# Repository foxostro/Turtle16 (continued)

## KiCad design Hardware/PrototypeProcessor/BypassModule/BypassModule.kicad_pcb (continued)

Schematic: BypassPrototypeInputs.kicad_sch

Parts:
J1: Control Signals; PinHeader_1x10_P2.54mm_Vertical
J2: Y_EX; PinHeader_1x16_P2.54mm_Vertical
J3: Y_MEM; PinHeader_1x16_P2.54mm_Vertical
J4: RegisterA; PinHeader_1x16_P2.54mm_Vertical
J5: RegisterB; PinHeader_1x16_P2.54mm_Vertical

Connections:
/Bypass Prototype Inputs/FWD_A: J1.3; also elsewhere on the board
/Bypass Prototype Inputs/FWD_B: J1.6; also elsewhere on the board
/Bypass Prototype Inputs/FWD_EX_TO_A: J1.4; also elsewhere on the board
/Bypass Prototype Inputs/FWD_EX_TO_B: J1.7; also elsewhere on the board
/Bypass Prototype Inputs/FWD_MEM_TO_A: J1.5; also elsewhere on the board
/Bypass Prototype Inputs/FWD_MEM_TO_B: J1.8; also elsewhere on the board
/Bypass Prototype Inputs/Phi1d: J1.1; also elsewhere on the board
/Bypass Prototype Inputs/RegisterA0: J4.1; also elsewhere on the board
/Bypass Prototype Inputs/RegisterA1: J4.2; also elsewhere on the board
/Bypass Prototype Inputs/RegisterA2: J4.3; also elsewhere on the board
/Bypass Prototype Inputs/RegisterA3: J4.4; also elsewhere on the board
/Bypass Prototype Inputs/RegisterA4: J4.5; also elsewhere on the board
/Bypass Prototype Inputs/RegisterA5: J4.6; also elsewhere on the board
/Bypass Prototype Inputs/RegisterA6: J4.7; also elsewhere on the board
/Bypass Prototype Inputs/RegisterA7: J4.8; also elsewhere on the board
/Bypass Prototype Inputs/RegisterA8: J4.9; also elsewhere on the board
/Bypass Prototype Inputs/RegisterA9: J4.10; also elsewhere on the board
/Bypass Prototype Inputs/RegisterA10: J4.11; also elsewhere on the board
/Bypass Prototype Inputs/RegisterA11: J4.12; also elsewhere on the board
/Bypass Prototype Inputs/RegisterA12: J4.13; also elsewhere on the board
/Bypass Prototype Inputs/RegisterA13: J4.14; also elsewhere on the board
/Bypass Prototype Inputs/RegisterA14: J4.15; also elsewhere on the board
/Bypass Prototype Inputs/RegisterA15: J4.16; also elsewhere on the board
/Bypass Prototype Inputs/RegisterB0: J5.1; also elsewhere on the board
/Bypass Prototype Inputs/RegisterB1: J5.2; also elsewhere on the board
/Bypass Prototype Inputs/RegisterB2: J5.3; also elsewhere on the board
/Bypass Prototype Inputs/RegisterB3: J5.4; also elsewhere on the board
/Bypass Prototype Inputs/RegisterB4: J5.5; also elsewhere on the board
/Bypass Prototype Inputs/RegisterB5: J5.6; also elsewhere on the board
/Bypass Prototype Inputs/RegisterB6: J5.7; also elsewhere on the board
/Bypass Prototype Inputs/RegisterB7: J5.8; also elsewhere on the board
/Bypass Prototype Inputs/RegisterB8: J5.9; also elsewhere on the board
/Bypass Prototype Inputs/RegisterB9: J5.10; also elsewhere on the board
/Bypass Prototype Inputs/RegisterB10: J5.11; also elsewhere on the board
/Bypass Prototype Inputs/RegisterB11: J5.12; also elsewhere on the board
/Bypass Prototype Inputs/RegisterB12: J5.13; also elsewhere on the board
/Bypass Prototype Inputs/RegisterB13: J5.14; also elsewhere on the board
/Bypass Prototype Inputs/RegisterB14: J5.15; also elsewhere on the board
/Bypass Prototype Inputs/RegisterB15: J5.16; also elsewhere on the board
/Bypass Prototype Inputs/Y_EX0: J2.1; also elsewhere on the board
/Bypass Prototype Inputs/Y_EX1: J2.2; also elsewhere on the board
/Bypass Prototype Inputs/Y_EX2: J2.3; also elsewhere on the board
/Bypass Prototype Inputs/Y_EX3: J2.4; also elsewhere on the board
/Bypass Prototype Inputs/Y_EX4: J2.5; also elsewhere on the board
/Bypass Prototype Inputs/Y_EX5: J2.6; also elsewhere on the board
/Bypass Prototype Inputs/Y_EX6: J2.7; also elsewhere on the board
/Bypass Prototype Inputs/Y_EX7: J2.8; also elsewhere on the board
/Bypass Prototype Inputs/Y_EX8: J2.9; also elsewhere on the board
/Bypass Prototype Inputs/Y_EX9: J2.10; also elsewhere on the board
/Bypass Prototype Inputs/Y_EX10: J2.11; also elsewhere on the board
/Bypass Prototype Inputs/Y_EX11: J2.12; also elsewhere on the board
/Bypass Prototype Inputs/Y_EX12: J2.13; also elsewhere on the board
/Bypass Prototype Inputs/Y_EX13: J2.14; also elsewhere on the board
/Bypass Prototype Inputs/Y_EX14: J2.15; also elsewhere on the board
/Bypass Prototype Inputs/Y_EX15: J2.16; also elsewhere on the board
/Bypass Prototype Inputs/Y_MEM0: J3.1; also elsewhere on the board
/Bypass Prototype Inputs/Y_MEM1: J3.2; also elsewhere on the board
/Bypass Prototype Inputs/Y_MEM2: J3.3; also elsewhere on the board
/Bypass Prototype Inputs/Y_MEM3: J3.4; also elsewhere on the board
/Bypass Prototype Inputs/Y_MEM4: J3.5; also elsewhere on the board
/Bypass Prototype Inputs/Y_MEM5: J3.6; also elsewhere on the board
/Bypass Prototype Inputs/Y_MEM6: J3.7; also elsewhere on the board
/Bypass Prototype Inputs/Y_MEM7: J3.8; also elsewhere on the board
/Bypass Prototype Inputs/Y_MEM8: J3.9; also elsewhere on the board
/Bypass Prototype Inputs/Y_MEM9: J3.10; also elsewhere on the board
/Bypass Prototype Inputs/Y_MEM10: J3.11; also elsewhere on the board
/Bypass Prototype Inputs/Y_MEM11: J3.12; also elsewhere on the board
/Bypass Prototype Inputs/Y_MEM12: J3.13; also elsewhere on the board
/Bypass Prototype Inputs/Y_MEM13: J3.14; also elsewhere on the board
/Bypass Prototype Inputs/Y_MEM14: J3.15; also elsewhere on the board
/Bypass Prototype Inputs/Y_MEM15: J3.16; also elsewhere on the board
GND: J1.2, J1.10; also elsewhere on the board
VCC: J1.9; also elsewhere on the board

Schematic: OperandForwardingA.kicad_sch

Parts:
C2, C3, C4: 100nF; C_0603_1608Metric_Pad1.08x0.95mm_HandSolder
U1, U2, U3: 74AHCT16245; TSSOP-48_6.1x12.5mm_P0.5mm

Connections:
/Bypass Prototype Inputs/FWD_A: U1.25 (2~OE), U1.48 (1~OE); also elsewhere on the board
/Bypass Prototype Inputs/FWD_EX_TO_A: U2.25 (2~OE), U2.48 (1~OE); also elsewhere on the board
/Bypass Prototype Inputs/FWD_MEM_TO_A: U3.25 (2~OE), U3.48 (1~OE); also elsewhere on the board
/Bypass Prototype Inputs/RegisterA0: U1.47 (1A1); also elsewhere on the board
/Bypass Prototype Inputs/RegisterA1: U1.46 (1A2); also elsewhere on the board
/Bypass Prototype Inputs/RegisterA2: U1.44 (1A3); also elsewhere on the board
/Bypass Prototype Inputs/RegisterA3: U1.43 (1A4); also elsewhere on the board
/Bypass Prototype Inputs/RegisterA4: U1.41 (1A5); also elsewhere on the board
/Bypass Prototype Inputs/RegisterA5: U1.40 (1A6); also elsewhere on the board
/Bypass Prototype Inputs/RegisterA6: U1.38 (1A7); also elsewhere on the board
/Bypass Prototype Inputs/RegisterA7: U1.37 (1A8); also elsewhere on the board
/Bypass Prototype Inputs/RegisterA8: U1.36 (2A1); also elsewhere on the board
/Bypass Prototype Inputs/RegisterA9: U1.35 (2A2); also elsewhere on the board
/Bypass Prototype Inputs/RegisterA10: U1.33 (2A3); also elsewhere on the board
/Bypass Prototype Inputs/RegisterA11: U1.32 (2A4); also elsewhere on the board
/Bypass Prototype Inputs/RegisterA12: U1.30 (2A5); also elsewhere on the board
/Bypass Prototype Inputs/RegisterA13: U1.29 (2A6); also elsewhere on the board
/Bypass Prototype Inputs/RegisterA14: U1.27 (2A7); also elsewhere on the board
/Bypass Prototype Inputs/RegisterA15: U1.26 (2A8); also elsewhere on the board
/Bypass Prototype Inputs/Y_EX0: U2.47 (1A1); also elsewhere on the board
/Bypass Prototype Inputs/Y_EX1: U2.46 (1A2); also elsewhere on the board
/Bypass Prototype Inputs/Y_EX2: U2.44 (1A3); also elsewhere on the board
/Bypass Prototype Inputs/Y_EX3: U2.43 (1A4); also elsewhere on the board
/Bypass Prototype Inputs/Y_EX4: U2.41 (1A5); also elsewhere on the board
/Bypass Prototype Inputs/Y_EX5: U2.40 (1A6); also elsewhere on the board
/Bypass Prototype Inputs/Y_EX6: U2.38 (1A7); also elsewhere on the board
/Bypass Prototype Inputs/Y_EX7: U2.37 (1A8); also elsewhere on the board
/Bypass Prototype Inputs/Y_EX8: U2.36 (2A1); also elsewhere on the board
/Bypass Prototype Inputs/Y_EX9: U2.35 (2A2); also elsewhere on the board
/Bypass Prototype Inputs/Y_EX10: U2.33 (2A3); also elsewhere on the board
/Bypass Prototype Inputs/Y_EX11: U2.32 (2A4); also elsewhere on the board
/Bypass Prototype Inputs/Y_EX12: U2.30 (2A5); also elsewhere on the board
/Bypass Prototype Inputs/Y_EX13: U2.29 (2A6); also elsewhere on the board
/Bypass Prototype Inputs/Y_EX14: U2.27 (2A7); also elsewhere on the board
/Bypass Prototype Inputs/Y_EX15: U2.26 (2A8); also elsewhere on the board
/Bypass Prototype Inputs/Y_MEM0: U3.47 (1A1); also elsewhere on the board
/Bypass Prototype Inputs/Y_MEM1: U3.46 (1A2); also elsewhere on the board
/Bypass Prototype Inputs/Y_MEM2: U3.44 (1A3); also elsewhere on the board
/Bypass Prototype Inputs/Y_MEM3: U3.43 (1A4); also elsewhere on the board
/Bypass Prototype Inputs/Y_MEM4: U3.41 (1A5); also elsewhere on the board
/Bypass Prototype Inputs/Y_MEM5: U3.40 (1A6); also elsewhere on the board
/Bypass Prototype Inputs/Y_MEM6: U3.38 (1A7); also elsewhere on the board
/Bypass Prototype Inputs/Y_MEM7: U3.37 (1A8); also elsewhere on the board
/Bypass Prototype Inputs/Y_MEM8: U3.36 (2A1); also elsewhere on the board
/Bypass Prototype Inputs/Y_MEM9: U3.35 (2A2); also elsewhere on the board
/Bypass Prototype Inputs/Y_MEM10: U3.33 (2A3); also elsewhere on the board
/Bypass Prototype Inputs/Y_MEM11: U3.32 (2A4); also elsewhere on the board
/Bypass Prototype Inputs/Y_MEM12: U3.30 (2A5); also elsewhere on the board
/Bypass Prototype Inputs/Y_MEM13: U3.29 (2A6); also elsewhere on the board
/Bypass Prototype Inputs/Y_MEM14: U3.27 (2A7); also elsewhere on the board
/Bypass Prototype Inputs/Y_MEM15: U3.26 (2A8); also elsewhere on the board
/Operand Forwarding A/A_ID0: U1.2 (1B1), U2.2 (1B1), U3.2 (1B1); also elsewhere on the board
/Operand Forwarding A/A_ID1: U1.3 (1B2), U2.3 (1B2), U3.3 (1B2); also elsewhere on the board
/Operand Forwarding A/A_ID2: U1.5 (1B3), U2.5 (1B3), U3.5 (1B3); also elsewhere on the board
/Operand Forwarding A/A_ID3: U1.6 (1B4), U2.6 (1B4), U3.6 (1B4); also elsewhere on the board
/Operand Forwarding A/A_ID4: U1.8 (1B5), U2.8 (1B5), U3.8 (1B5); also elsewhere on the board
/Operand Forwarding A/A_ID5: U1.9 (1B6), U2.9 (1B6), U3.9 (1B6); also elsewhere on the board
/Operand Forwarding A/A_ID6: U1.11 (1B7), U2.11 (1B7), U3.11 (1B7); also elsewhere on the board
/Operand Forwarding A/A_ID7: U1.12 (1B8), U2.12 (1B8), U3.12 (1B8); also elsewhere on the board
/Operand Forwarding A/A_ID8: U1.13 (2B1), U2.13 (2B1), U3.13 (2B1); also elsewhere on the board
/Operand Forwarding A/A_ID9: U1.14 (2B2), U2.14 (2B2), U3.14 (2B2); also elsewhere on the board
/Operand Forwarding A/A_ID10: U1.16 (2B3), U2.16 (2B3), U3.16 (2B3); also elsewhere on the board
/Operand Forwarding A/A_ID11: U1.17 (2B4), U2.17 (2B4), U3.17 (2B4); also elsewhere on the board
/Operand Forwarding A/A_ID12: U1.19 (2B5), U2.19 (2B5), U3.19 (2B5); also elsewhere on the board
/Operand Forwarding A/A_ID13: U1.20 (2B6), U2.20 (2B6), U3.20 (2B6); also elsewhere on the board
/Operand Forwarding A/A_ID14: U1.22 (2B7), U2.22 (2B7), U3.22 (2B7); also elsewhere on the board
/Operand Forwarding A/A_ID15: U1.23 (2B8), U2.23 (2B8), U3.23 (2B8); also elsewhere on the board
GND: C2.2, C3.2, C4.2, U1.4 (GND), U1.10 (GND), U1.15 (GND), U1.21 (GND), U1.28 (GND), U1.34 (GND), U1.39 (GND), U1.45 (GND), U2.4 (GND), U2.10 (GND), U2.15 (GND), U2.21 (GND), U2.28 (GND), U2.34 (GND), U2.39 (GND), U2.45 (GND), U3.4 (GND), U3.10 (GND), U3.15 (GND), U3.21 (GND), U3.28 (GND), U3.34 (GND), U3.39 (GND), U3.45 (GND); also elsewhere on the board
VCC: C2.1, C3.1, C4.1, U1.1 (1DIR), U1.7 (VCC), U1.18 (VCC), U1.24 (2DIR), U1.31 (VCC), U1.42 (VCC), U2.1 (1DIR), U2.7 (VCC), U2.18 (VCC), U2.24 (2DIR), U2.31 (VCC), U2.42 (VCC), U3.1 (1DIR), U3.7 (VCC), U3.18 (VCC), U3.24 (2DIR), U3.31 (VCC), U3.42 (VCC); also elsewhere on the board

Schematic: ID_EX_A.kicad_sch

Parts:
C8: 100nF; C_0603_1608Metric_Pad1.08x0.95mm_HandSolder
U7: 74ABT16374; TSSOP-48_6.1x12.5mm_P0.5mm

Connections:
/Bypass Prototype Inputs/Phi1d: U7.25 (2CLK), U7.48 (1CLK); also elsewhere on the board
/BypassPrototypeOutputs/A0: U7.2 (1Q1); also elsewhere on the board
/BypassPrototypeOutputs/A1: U7.3 (1Q2); also elsewhere on the board
/BypassPrototypeOutputs/A2: U7.5 (1Q3); also elsewhere on the board
/BypassPrototypeOutputs/A3: U7.6 (1Q4); also elsewhere on the board
/BypassPrototypeOutputs/A4: U7.8 (1Q5); also elsewhere on the board
/BypassPrototypeOutputs/A5: U7.9 (1Q6); also elsewhere on the board
/BypassPrototypeOutputs/A6: U7.11 (1Q7); also elsewhere on the board
/BypassPrototypeOutputs/A7: U7.12 (1Q8); also elsewhere on the board
/BypassPrototypeOutputs/A8: U7.13 (2Q1); also elsewhere on the board
/BypassPrototypeOutputs/A9: U7.14 (2Q2); also elsewhere on the board
/BypassPrototypeOutputs/A10: U7.16 (2Q3); also elsewhere on the board
/BypassPrototypeOutputs/A11: U7.17 (2Q4); also elsewhere on the board
/BypassPrototypeOutputs/A12: U7.19 (2Q5); also elsewhere on the board
/BypassPrototypeOutputs/A13: U7.20 (2Q6); also elsewhere on the board
/BypassPrototypeOutputs/A14: U7.22 (2Q7); also elsewhere on the board
/BypassPrototypeOutputs/A15: U7.23 (2Q8); also elsewhere on the board
/Operand Forwarding A/A_ID0: U7.47 (1D1); also elsewhere on the board
/Operand Forwarding A/A_ID1: U7.46 (1D2); also elsewhere on the board
/Operand Forwarding A/A_ID2: U7.44 (1D3); also elsewhere on the board
/Operand Forwarding A/A_ID3: U7.43 (1D4); also elsewhere on the board
/Operand Forwarding A/A_ID4: U7.41 (1D5); also elsewhere on the board
/Operand Forwarding A/A_ID5: U7.40 (1D6); also elsewhere on the board
/Operand Forwarding A/A_ID6: U7.38 (1D7); also elsewhere on the board
/Operand Forwarding A/A_ID7: U7.37 (1D8); also elsewhere on the board
/Operand Forwarding A/A_ID8: U7.36 (2D1); also elsewhere on the board
/Operand Forwarding A/A_ID9: U7.35 (2D2); also elsewhere on the board
/Operand Forwarding A/A_ID10: U7.33 (2D3); also elsewhere on the board
/Operand Forwarding A/A_ID11: U7.32 (2D4); also elsewhere on the board
/Operand Forwarding A/A_ID12: U7.30 (2D5); also elsewhere on the board
/Operand Forwarding A/A_ID13: U7.29 (2D6); also elsewhere on the board
/Operand Forwarding A/A_ID14: U7.27 (2D7); also elsewhere on the board
/Operand Forwarding A/A_ID15: U7.26 (2D8); also elsewhere on the board
GND: C8.2, U7.1 (1~OE), U7.4 (GND), U7.10 (GND), U7.15 (GND), U7.21 (GND), U7.24 (2~OE), U7.28 (GND), U7.34 (GND), U7.39 (GND), U7.45 (GND); also elsewhere on the board
VCC: C8.1, U7.7 (VCC), U7.18 (VCC), U7.31 (VCC), U7.42 (VCC); also elsewhere on the board

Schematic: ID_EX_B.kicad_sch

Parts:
C9: 100nF; C_0603_1608Metric_Pad1.08x0.95mm_HandSolder
U8: 74ABT16374; TSSOP-48_6.1x12.5mm_P0.5mm

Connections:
/Bypass Prototype Inputs/Phi1d: U8.25 (2CLK), U8.48 (1CLK); also elsewhere on the board
/BypassPrototypeOutputs/B0: U8.2 (1Q1); also elsewhere on the board
/BypassPrototypeOutputs/B1: U8.3 (1Q2); also elsewhere on the board
/BypassPrototypeOutputs/B2: U8.5 (1Q3); also elsewhere on the board
/BypassPrototypeOutputs/B3: U8.6 (1Q4); also elsewhere on the board
/BypassPrototypeOutputs/B4: U8.8 (1Q5); also elsewhere on the board
/BypassPrototypeOutputs/B5: U8.9 (1Q6); also elsewhere on the board
/BypassPrototypeOutputs/B6: U8.11 (1Q7); also elsewhere on the board
/BypassPrototypeOutputs/B7: U8.12 (1Q8); also elsewhere on the board
/BypassPrototypeOutputs/B8: U8.13 (2Q1); also elsewhere on the board
/BypassPrototypeOutputs/B9: U8.14 (2Q2); also elsewhere on the board
/BypassPrototypeOutputs/B10: U8.16 (2Q3); also elsewhere on the board
/BypassPrototypeOutputs/B11: U8.17 (2Q4); also elsewhere on the board
/BypassPrototypeOutputs/B12: U8.19 (2Q5); also elsewhere on the board
/BypassPrototypeOutputs/B13: U8.20 (2Q6); also elsewhere on the board
/BypassPrototypeOutputs/B14: U8.22 (2Q7); also elsewhere on the board
/BypassPrototypeOutputs/B15: U8.23 (2Q8); also elsewhere on the board
/Operand Forwarding B/B_ID0: U8.47 (1D1); also elsewhere on the board
/Operand Forwarding B/B_ID1: U8.46 (1D2); also elsewhere on the board
/Operand Forwarding B/B_ID2: U8.44 (1D3); also elsewhere on the board
/Operand Forwarding B/B_ID3: U8.43 (1D4); also elsewhere on the board
/Operand Forwarding B/B_ID4: U8.41 (1D5); also elsewhere on the board
/Operand Forwarding B/B_ID5: U8.40 (1D6); also elsewhere on the board
/Operand Forwarding B/B_ID6: U8.38 (1D7); also elsewhere on the board
/Operand Forwarding B/B_ID7: U8.37 (1D8); also elsewhere on the board
/Operand Forwarding B/B_ID8: U8.36 (2D1); also elsewhere on the board
/Operand Forwarding B/B_ID9: U8.35 (2D2); also elsewhere on the board
/Operand Forwarding B/B_ID10: U8.33 (2D3); also elsewhere on the board
/Operand Forwarding B/B_ID11: U8.32 (2D4); also elsewhere on the board
/Operand Forwarding B/B_ID12: U8.30 (2D5); also elsewhere on the board
/Operand Forwarding B/B_ID13: U8.29 (2D6); also elsewhere on the board
/Operand Forwarding B/B_ID14: U8.27 (2D7); also elsewhere on the board
/Operand Forwarding B/B_ID15: U8.26 (2D8); also elsewhere on the board
GND: C9.2, U8.1 (1~OE), U8.4 (GND), U8.10 (GND), U8.15 (GND), U8.21 (GND), U8.24 (2~OE), U8.28 (GND), U8.34 (GND), U8.39 (GND), U8.45 (GND); also elsewhere on the board
VCC: C9.1, U8.7 (VCC), U8.18 (VCC), U8.31 (VCC), U8.42 (VCC); also elsewhere on the board

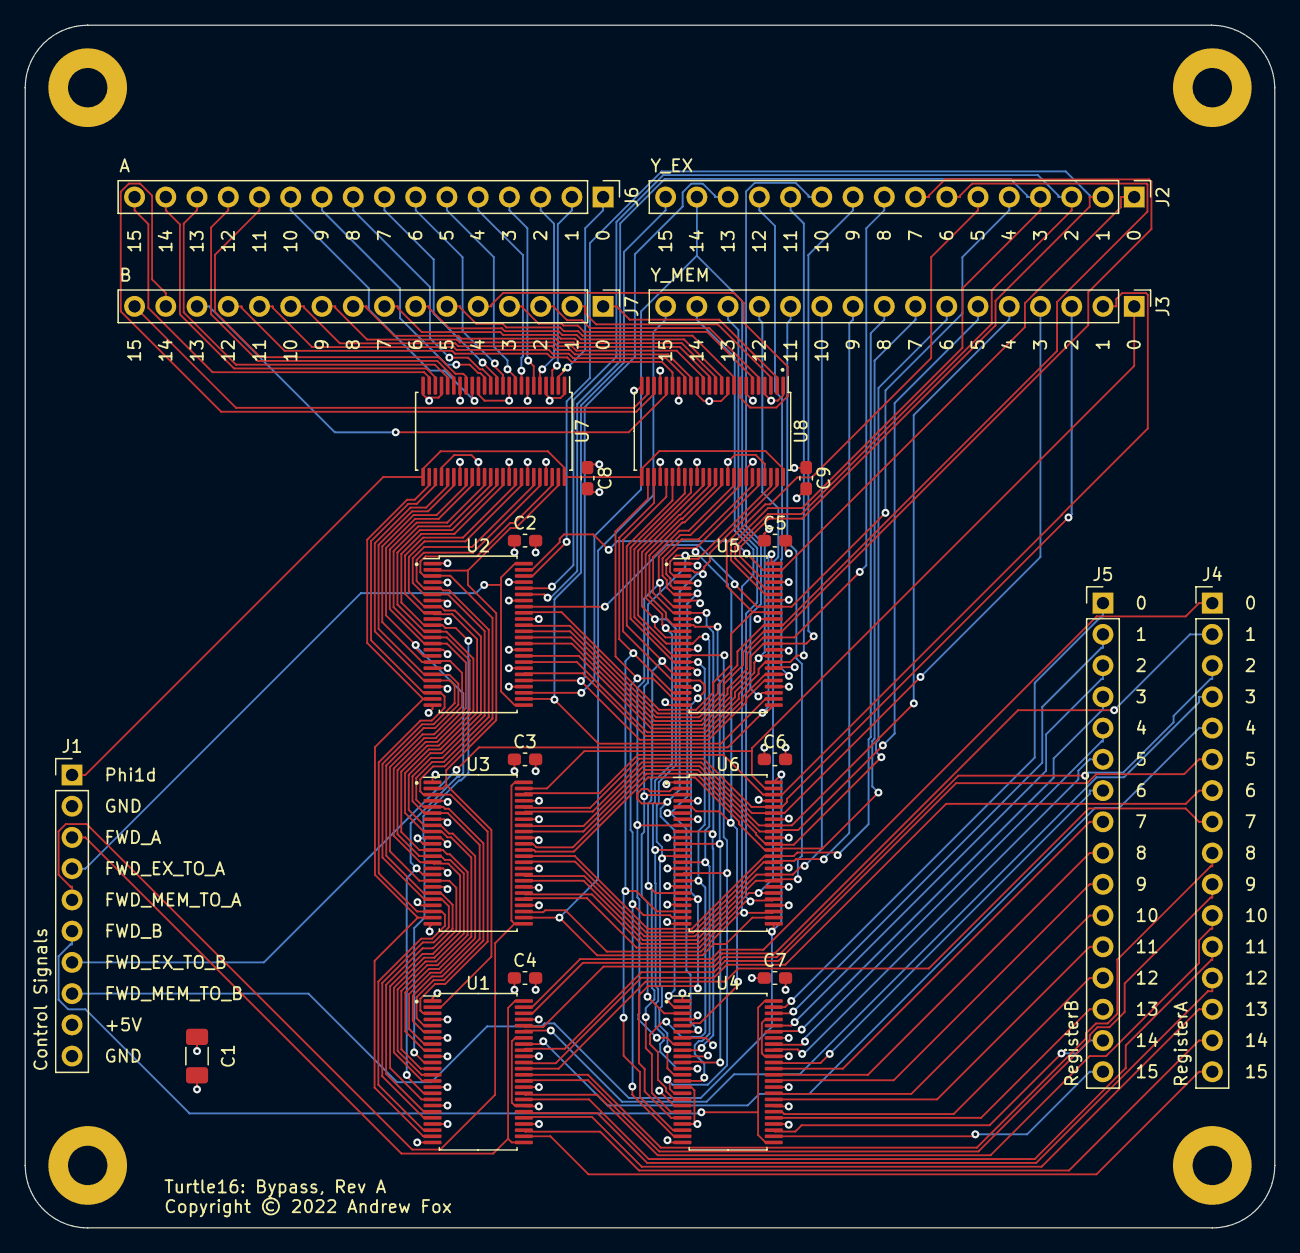
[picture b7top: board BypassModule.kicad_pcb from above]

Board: 4 copper layers, 101.6 x 97.8 mm, 28 parts (0 on the bottom side), 137 nets.

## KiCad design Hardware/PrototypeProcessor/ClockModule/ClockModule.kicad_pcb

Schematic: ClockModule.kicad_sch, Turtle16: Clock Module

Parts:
C1: 100µF; C_1206_3216Metric_Pad1.33x1.80mm_HandSolder
H1, H2, H3, H4: MountingHole_Pad; MountingHole_3.2mm_M3_Pad
J1: Clock Inputs; PinHeader_1x06_P2.54mm_Vertical
J2: Clock Outputs; PinHeader_1x06_P2.54mm_Vertical
J3: GND; PinHeader_1x06_P2.54mm_Vertical
J4: Single Step; PinHeader_1x03_P2.54mm_Vertical

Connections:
/Clock/Phi1a: J2.1; also elsewhere on the board
/Clock/Phi1b: J2.2; also elsewhere on the board
/Clock/Phi1c: J2.3; also elsewhere on the board
/Clock/Phi1d: J2.4; also elsewhere on the board
/Clock/Phi2: J2.5; also elsewhere on the board
/Clock/RDY: J1.4; also elsewhere on the board
/Clock/RawClock: J1.1; also elsewhere on the board
/Clock/~HLT: J1.2; also elsewhere on the board
/Clock/~RST_sync: J2.6; also elsewhere on the board
/Clock/~SINGLE: J1.3, J4.2; also elsewhere on the board
GND: C1.2, H1.1, H2.1, H3.1, H4.1, J1.6, J3.1, J3.2, J3.3, J3.4, J3.5, J3.6, J4.3; also elsewhere on the board
VCC: C1.1, J1.5, J4.1; also elsewhere on the board

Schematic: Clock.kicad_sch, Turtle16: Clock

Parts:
C2, C3, C4, C5, C6, C7: 0.1µF; C_0603_1608Metric_Pad1.08x0.95mm_HandSolder
C9: 1uF; C_0603_1608Metric_Pad1.08x0.95mm_HandSolder
D1: Halt; LED_0805_2012Metric
D2: Power OK; LED_0805_2012Metric
D3: Wait; LED_0805_2012Metric
OSC1: 12MHz; Oscillator_DIP-14
R1, R3, R7: 270R; C_0603_1608Metric
R2, R5: 1K; R_0603_1608Metric_Pad0.98x0.95mm_HandSolder
R4, R6: 10K; R_0603_1608Metric_Pad0.98x0.95mm_HandSolder
SW1: Reset; SW_PUSH_6mm_H5mm
SW2: Resume; SW_PUSH_6mm_H5mm
TP1: ~{HLT}; TestPoint_Pad_D1.0mm
TP2: RawClock; TestPoint_Pad_D1.0mm
TP3: Phi0; TestPoint_Pad_D1.0mm
TP4: TestPoint_Pad_D1.0mm
TP5, TP6, TP14, TP17: TP; TestPoint_Pad_D1.0mm
TP7: ~{RST_sync}; TestPoint_Pad_D1.0mm
TP8: Phi2; TestPoint_Pad_D1.0mm
TP9: ~{RST_async}; TestPoint_Pad_D1.0mm
TP10: Phi1a; TestPoint_Pad_D1.0mm
TP11: Phi1b; TestPoint_Pad_D1.0mm
TP12: Phi1c; TestPoint_Pad_D1.0mm
TP13: Phi1d; TestPoint_Pad_D1.0mm
TP15: Resume; TestPoint_Pad_D1.0mm
TP16: RDY; TestPoint_Pad_D1.0mm
TP18: Debounced; TestPoint_Pad_D1.0mm
U2: 74AHCT04; TSSOP-14_4.4x5mm_P0.65mm
U3: ATF22V10C; DIP-24_W7.62mm_Socket
U4: 74AHCT05; TSSOP-14_4.4x5mm_P0.65mm
U5: 74AHCT245; TSSOP-20_4.4x6.5mm_P0.65mm
U6: MCP100-450D; TO-92

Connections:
/Clock/Button0: TP18.1, U3.5 (IN), U5.11 (B7)
/Clock/ButtonRC: C9.1, R5.1, TP17.1, U5.9 (A7)
/Clock/NOT_RDY: TP14.1, U3.20 (I/O), U4.1
/Clock/Phi0: TP3.1, U3.1 (IN/CLK), U5.12 (B6)
/Clock/Phi1: TP4.1, U3.23 (I/O), U5.4 (A2), U5.5 (A3), U5.6 (A4), U5.7 (A5)
/Clock/Phi1a: TP10.1, U5.16 (B2); also elsewhere on the board
/Clock/Phi1b: TP11.1, U5.15 (B3); also elsewhere on the board
/Clock/Phi1c: TP12.1, U5.14 (B4); also elsewhere on the board
/Clock/Phi1d: TP13.1, U5.13 (B5); also elsewhere on the board
/Clock/Phi2: TP8.1, U5.17 (B1); also elsewhere on the board
/Clock/Phi2_0: TP5.1, U3.22 (I/O), U5.3 (A1)
/Clock/RDY: R6.2, TP16.1, U2.1, U3.6 (IN), U4.2; also elsewhere on the board
/Clock/RawClock: OSC1.8 (OUT), TP2.1, U5.8 (A6); also elsewhere on the board
/Clock//RST_sync0: TP6.1, U3.21 (I/O), U5.2 (A0)
/Clock/~HLT: TP1.1, U2.5, U3.3 (IN); also elsewhere on the board
/Clock/~RST_async: TP9.1, U2.13, U3.4 (IN), U6.1 (~RST)
/Clock/~RST_sync: TP7.1, U5.18 (B0); also elsewhere on the board
/Clock/~SINGLE: U3.2 (IN); also elsewhere on the board
GND: C2.2, C3.2, C4.2, C5.2, C6.2, C7.2, C9.2, OSC1.7 (GND), R1.2, R3.2, R7.2, SW1.1, SW2.1, U2.7 (GND), U3.12 (GND), U4.7 (GND), U5.10 (GND), U5.19 (CE), U6.3 (VSS); also elsewhere on the board
unnamed: D1.2 (A), U2.6
unnamed: D1.1 (K), R1.1
unnamed: D2.2 (A), U2.10
unnamed: D2.1 (K), R3.1
unnamed: D3.2 (A), U2.2
unnamed: D3.1 (K), R7.1
unnamed: R4.2, R5.2, SW2.2, TP15.1
unnamed: U2.11, U2.12
unnamed: R2.2, SW1.2, U6.2 (VDD)
VCC: C2.1, C3.1, C4.1, C5.1, C6.1, C7.1, OSC1.14 (Vcc), R2.1, R4.1, R6.1, U2.3, U2.9, U2.14 (VCC), U3.24 (VCC), U4.3, U4.5, U4.9, U4.11, U4.13, U4.14 (VCC), U5.1 (A->B), U5.20 (VCC); also elsewhere on the board

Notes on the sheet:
~{RST_sync} goes Low asynchronously as soon as the register is reset. The rising edge is always synchronous.
RDY is a shared, open collector line which signals that the computer is ready for execution. The clock, or another device may halt execution by pulling the line low.
The inverters buffer the Reset signal.
RDY needs a strong pull-up to ensure the signal rises from Low to High quickly.
The Phi1 clock is split into four clock outputs to allow clock line capacitance and current load to be spread across multiple pins.
Schmitt trigger converts a slow rising sine clock to a fast logic edge. This is more important when driving RawClock from the input connector than when an oscillator can is in the socket.
Unused devices
While the ~{HLT} line is active, the Resume button will allow the clock to tick one time per button press. Assert ~{SINGLE} to allow single- step with the Resume button.
Decoupling capacitors

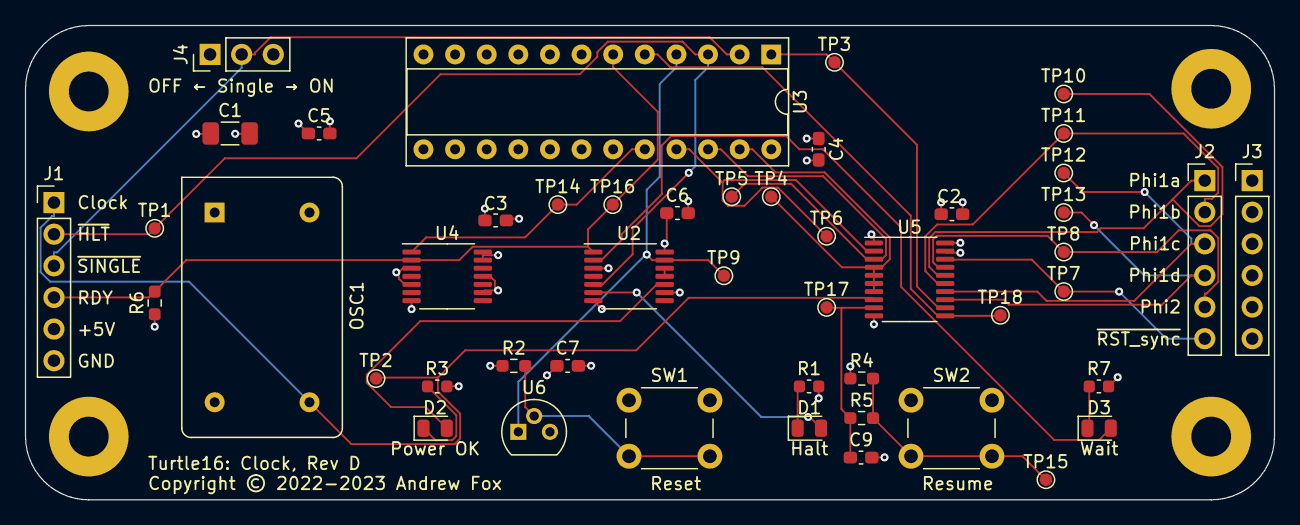
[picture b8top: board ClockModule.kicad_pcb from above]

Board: 4 copper layers, 100.3 x 38.1 mm, 52 parts (0 on the bottom side), 29 nets.
